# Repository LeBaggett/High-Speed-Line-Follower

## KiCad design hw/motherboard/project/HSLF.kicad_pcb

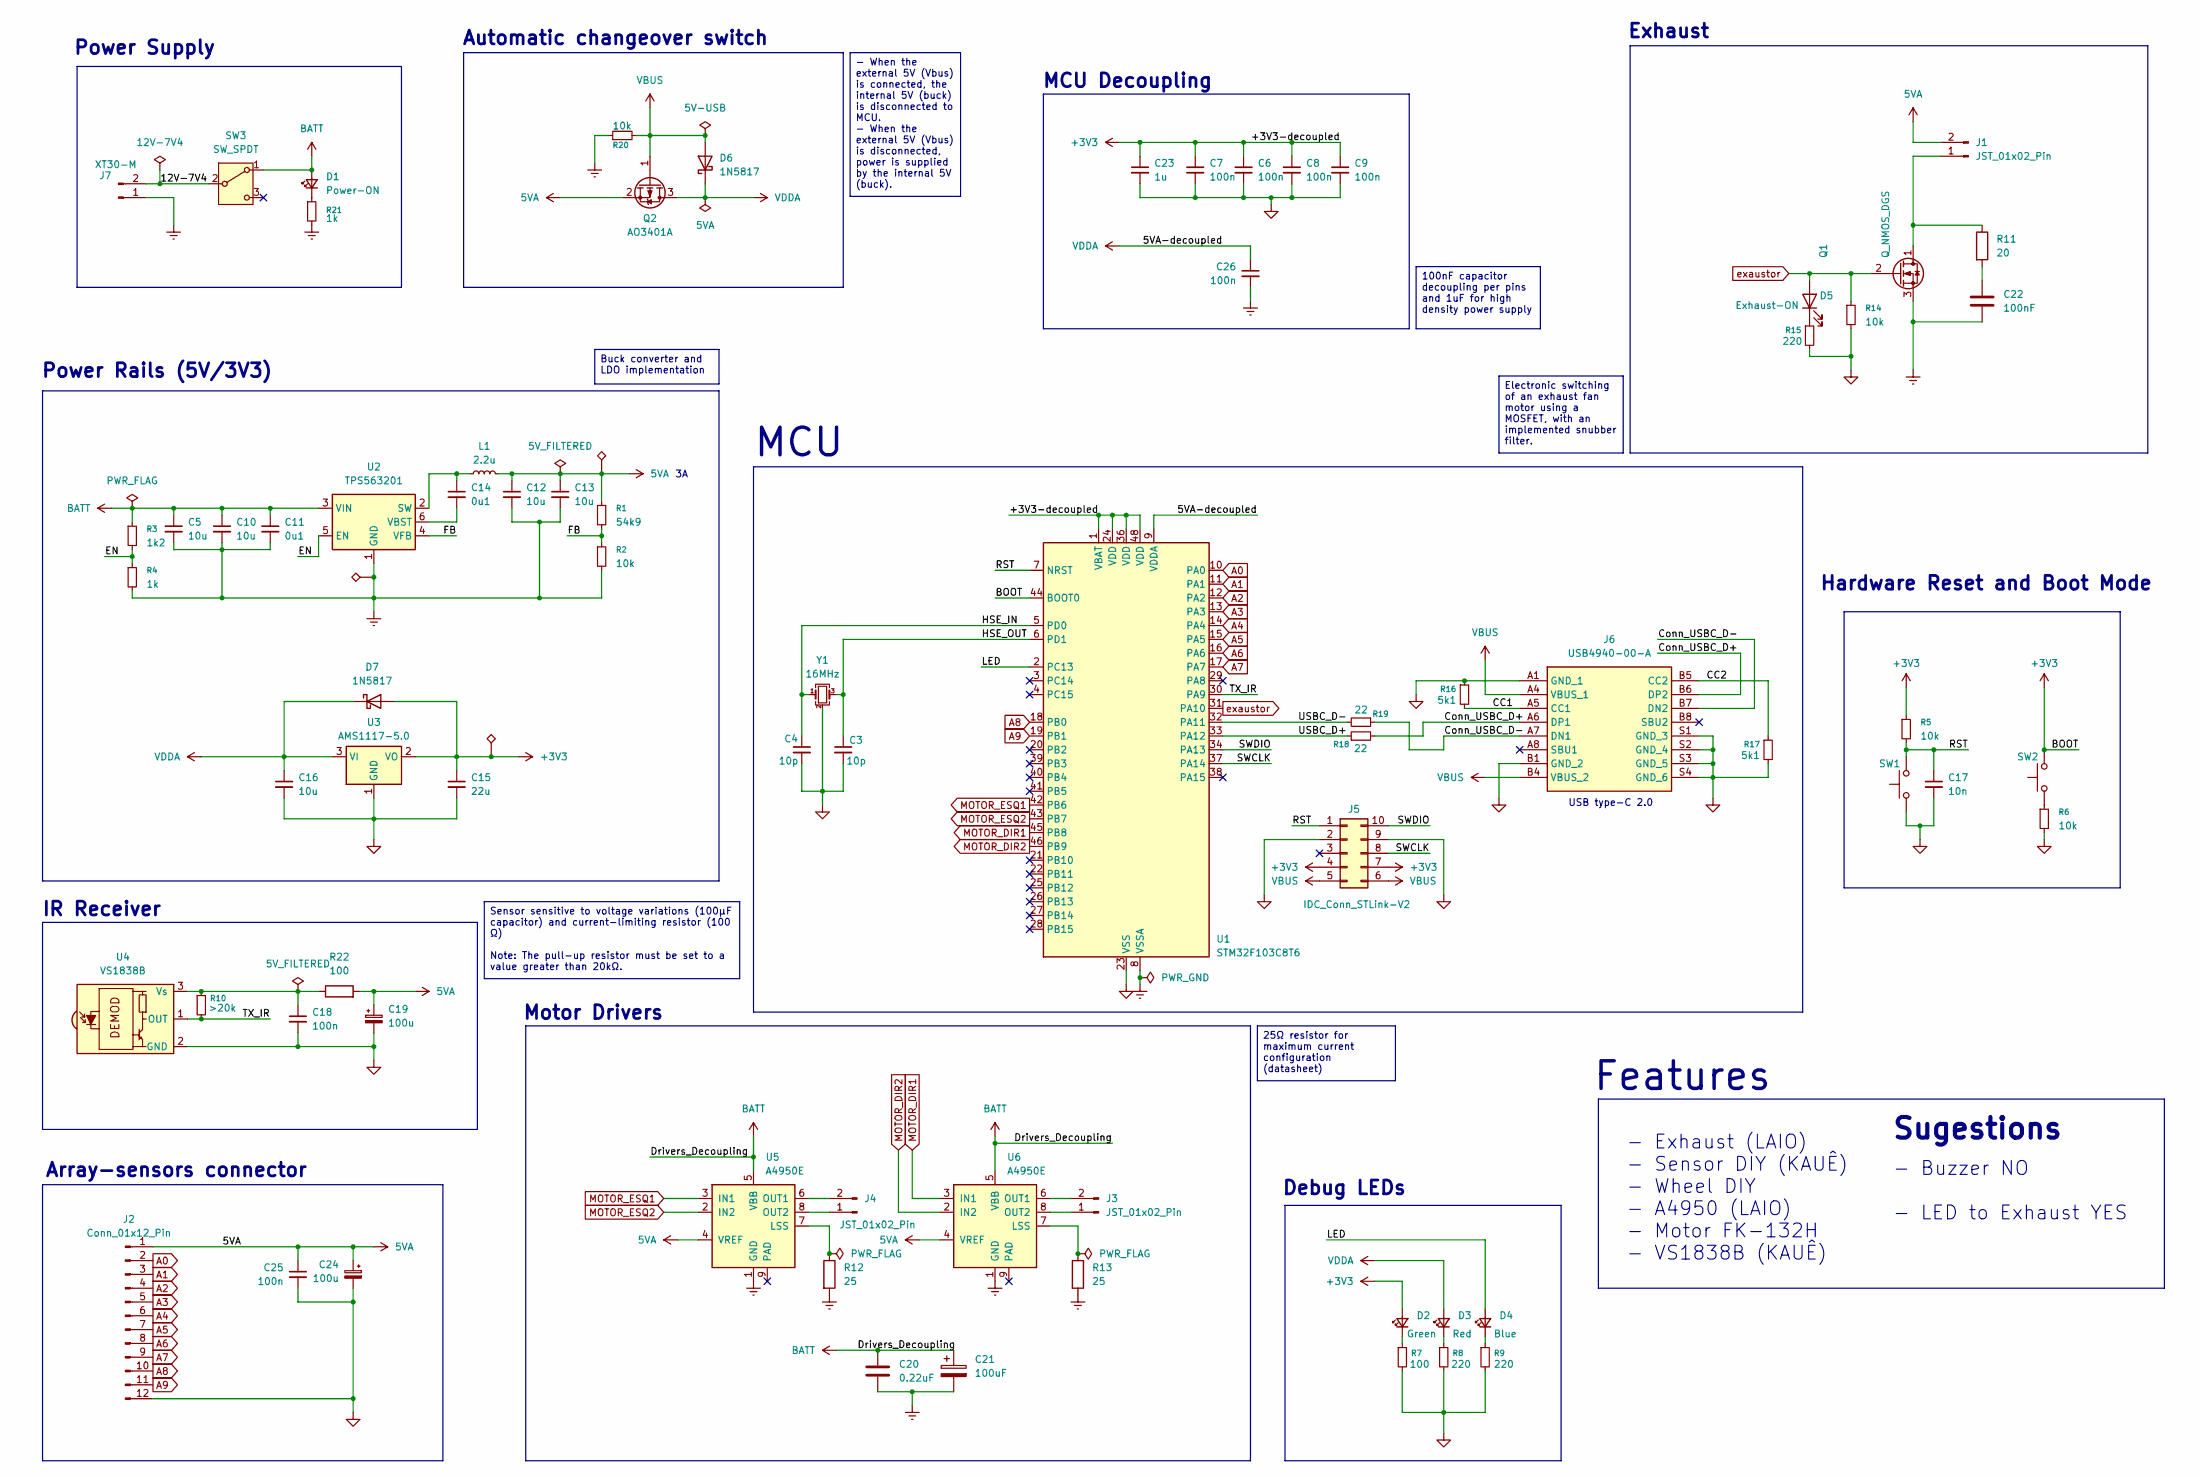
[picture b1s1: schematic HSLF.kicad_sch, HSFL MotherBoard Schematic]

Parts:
C3, C4: 10p; C_0805_2012Metric_Pad1.18x1.45mm_HandSolder
C5, C10, C12, C13, C16: 10u; C_0805_2012Metric_Pad1.18x1.45mm_HandSolder
C6, C7, C8, C9, C18, C25, C26: 100n; C_0805_2012Metric_Pad1.18x1.45mm_HandSolder
C11, C14: 0u1; C_0805_2012Metric_Pad1.18x1.45mm_HandSolder
C15: 22u; C_0805_2012Metric_Pad1.18x1.45mm_HandSolder
C17: 10n; C_0805_2012Metric_Pad1.18x1.45mm_HandSolder
C19: 100u; CP_Elec_5x3
C20: 0.22uF; C_0805_2012Metric_Pad1.18x1.45mm_HandSolder
C21: 100uF; CP_Elec_6.3x5.4
C22: 100nF; C_0805_2012Metric_Pad1.18x1.45mm_HandSolder
C23: 1u; C_0805_2012Metric_Pad1.18x1.45mm_HandSolder
C24: 100u; CP_Elec_6.3x5.4
D1: Power-ON; LED_1206_3216Metric_Pad1.42x1.75mm_HandSolder
D2: Green; LED_1206_3216Metric_Pad1.42x1.75mm_HandSolder
D3: Red; LED_1206_3216Metric_Pad1.42x1.75mm_HandSolder
D4: Blue; LED_1206_3216Metric_Pad1.42x1.75mm_HandSolder
D5: Exhaust-ON; LED_1206_3216Metric_Pad1.42x1.75mm_HandSolder
D6, D7: 1N5817; D_1206_3216Metric_Pad1.42x1.75mm_HandSolder
J1, J3, J4: JST_01x02_Pin; JST_XH_B2B-XH-A_1x02_P2.50mm_Vertical
J2: Conn_01x12_Pin; JST_XH_B12B-XH-A_1x12_P2.50mm_Vertical
J5: IDC_Conn_STLink-V2; IDC-Header_2x05_P2.54mm_Vertical
J6: USB4940-00-A; USB494000A; Manufacturer_Part_Number USB4940-00-A
J7: XT30-M; AMASS_XT30UPB-M_1x02_P5.0mm_Vertical
L1: 2.2u; L_APV_APH0618
Q1: Q_NMOS_DGS; TSOT-23_HandSoldering
Q2: AO3401A; SOT-23
R1: 54k9; R_0805_2012Metric_Pad1.20x1.40mm_HandSolder
R2, R5, R6, R14, R20: 10k; R_0805_2012Metric_Pad1.20x1.40mm_HandSolder
R3: 1k2; R_0805_2012Metric_Pad1.20x1.40mm_HandSolder
R4, R21: 1k; R_0805_2012Metric_Pad1.20x1.40mm_HandSolder
R7, R22: 100; R_0805_2012Metric_Pad1.20x1.40mm_HandSolder
R8, R9, R15: 220; R_0805_2012Metric_Pad1.20x1.40mm_HandSolder
R10: >20k; R_0805_2012Metric_Pad1.20x1.40mm_HandSolder
R11: 20; R_0805_2012Metric_Pad1.20x1.40mm_HandSolder
R12, R13: 25; R_0805_2012Metric_Pad1.20x1.40mm_HandSolder
R16, R17: 5k1; R_0805_2012Metric_Pad1.20x1.40mm_HandSolder
R18, R19: 22; R_0805_2012Metric_Pad1.20x1.40mm_HandSolder
SW1, SW2: SW_Push; SW_Push_1P1T_NO_E-Switch_TL3301NxxxxxG
SW3: SW_SPDT; SW_Slide_SPDT_Straight_CK_OS102011MS2Q
TP1, TP2, TP3: TestPoint_Alt; TestPoint_Pad_1.0x1.0mm
U1: STM32F103C8T6; LQFP-48_7x7mm_P0.5mm
U2: TPS563201; SOT-23-6_Handsoldering
U3: AMS1117-5.0; SOT-223-3_TabPin2
U4: VS1838B; Vishay_MOLD-3Pin
U5, U6: A4950E; SOIC-8-1EP_3.9x4.9mm_P1.27mm_EP2.41x3.3mm
Y1: 16MHz; Crystal_SMD_3225-4Pin_3.2x2.5mm_HandSoldering

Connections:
5VA: C12.1, C13.1, C19.1, C24.1, C25.1, J1.2, J2.1, L1.2, Q2.2 (S), R1.1, R22.2, TP2.1 (1_1), U5.4 (VREF), U6.4 (VREF)
+3V3: C6.1, C7.1, C8.1, C9.1, C15.1, C23.1, D2.2 (A), D7.2 (A), J5.4, J5.7, R5.1, SW2.2, TP3.1 (1_1), U1.1 (VBAT), U1.24 (VDD), U1.36 (VDD), U1.44 (BOOT0), U1.48 (VDD), U3.2 (VO)
/12V-7V4: J7.2, SW3.2 (B)
/CC1: J6.A5 (CC1), R16.2
/CC2: J6.B5 (CC2), R17.1
/Conn_USBC_D+: J6.A6 (DP1), J6.B6 (DP2), R18.2
/Conn_USBC_D-: J6.A7 (DN1), J6.B7 (DN2), R19.1
/EN: R3.2, R4.1, U2.5 (EN)
/FB: R1.2, R2.1, U2.4 (VFB)
/HSE_IN: C4.1, U1.5 (PD0), Y1.1
/HSE_OUT: C3.1, U1.6 (PD1), Y1.3
/LED: D4.2 (A), U1.2 (PC13)
/RST: C17.1, J5.1, R5.2, SW1.2, U1.7 (NRST)
/SWCLK: J5.8, U1.37 (PA14)
/SWDIO: J5.10, U1.34 (PA13)
/TX_IR: R10.2, U1.30 (PA9), U4.1 (OUT)
/USBC_D+: R18.1, U1.33 (PA12)
/USBC_D-: R19.2, U1.32 (PA11)
A0: J2.2, U1.10 (PA0)
A1: J2.3, U1.11 (PA1)
A2: J2.4, U1.12 (PA2)
A3: J2.5, U1.13 (PA3)
A4: J2.6, U1.14 (PA4)
A5: J2.7, U1.15 (PA5)
A6: J2.8, U1.16 (PA6)
A7: J2.9, U1.17 (PA7)
A8: J2.10, U1.18 (PB0)
A9: J2.11, U1.19 (PB1)
BATT: C5.1, C10.1, C11.1, C20.1, C21.1, D1.2 (A), R3.1, SW3.1 (A), U2.3 (VIN), U5.5 (VBB), U6.5 (VBB)
GND: C3.2, C4.2, C5.2, C6.2, C7.2, C8.2, C9.2, C10.2, C11.2, C12.2, C13.2, C15.2, C16.2, C17.2, C18.2, C19.2, C20.2, C21.2, C22.2, C23.2, C24.2, C25.2, C26.2, J2.12, J5.2, J5.9, J6.A1 (GND_1), J6.B1 (GND_2), J6.S1 (GND_3), J6.S2 (GND_4), J6.S3 (GND_5), J6.S4 (GND_6), J7.1, Q1.3 (S), R2.2, R4.2, R6.2, R7.2, R8.2, R9.2, R12.2, R13.2, R14.2, R15.2, R16.1, R17.2, R20.1, R21.2, SW1.1, TP1.1 (1_1), U1.8 (VSSA), U1.23 (VSS), U1.35 (VSS), U1.47 (VSS), U2.1 (GND), U3.1 (GND), U4.2 (GND), U5.1 (GND), U6.1 (GND), Y1.2 (G), Y1.4 (G)
MOTOR_DIR1: U1.45 (PB8), U6.3 (IN1)
MOTOR_DIR2: U1.46 (PB9), U6.2 (IN2)
MOTOR_ESQ1: U1.42 (PB6), U5.3 (IN1)
MOTOR_ESQ2: U1.43 (PB7), U5.2 (IN2)
unnamed: C22.1, R11.2
unnamed: D1.1 (K), R21.1
unnamed: D2.1 (K), R7.1
unnamed: D3.1 (K), R8.1
unnamed: D4.1 (K), R9.1
unnamed: D5.1 (K), R15.1
unnamed: J1.1, Q1.1 (D), R11.1
unnamed: J3.1, U6.8 (OUT2)
unnamed: J3.2, U6.6 (OUT1)
unnamed: J4.1, U5.8 (OUT2)
unnamed: J4.2, U5.6 (OUT1)
unnamed: R6.1, SW2.1
unnamed: C14.1, L1.1, U2.2 (SW)
unnamed: C14.2, U2.6 (VBST)
unnamed: C18.1, R10.1, R22.1, U4.3 (Vs)
unnamed: R12.1, U5.7 (LSS)
unnamed: R13.1, U6.7 (LSS)
VBUS: D6.2 (A), J5.5, J5.6, J6.A4 (VBUS_1), J6.B4 (VBUS_2), Q2.1 (G), R20.2
VDDA: C16.1, C26.1, D3.2 (A), D6.1 (K), D7.1 (K), Q2.3 (D), U1.9 (VDDA), U3.3 (VI)
exaustor: D5.2 (A), Q1.2 (G), R14.1, U1.31 (PA10)

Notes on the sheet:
Array-sensors connector
Hardware Reset and Boot Mode
MCU Decoupling
Features
USB type-C 2.0
Power Supply
Exhaust
- Exhaust (LAIO) - Sensor DIY (KAUÊ) - Wheel DIY - A4950 (LAIO) - Motor FK-132H - VS1838B (KAUÊ)
Motor Drivers
Power Rails (5V/3V3)
Debug LEDs
Automatic changeover switch
- Buzzer NO - LED to Exhaust YES
MCU
Sugestions
IR Receiver
- When the external 5V (Vbus) is connected, the internal 5V (buck) is disconnected to MCU. - When the external 5V (Vbus) is disconnected, power is supplied by the internal 5V (buck).
Electronic switching of an exhaust fan motor using a MOSFET, with an implemented snubber filter.
Sensor sensitive to voltage variations (100µF capacitor) and current-limiting resistor (100 Ω) Note: The pull-up resistor must be set to a value greater than 20kΩ.
100nF capacitor decoupling per pins and 1uF for high density power supply
Buck converter and LDO implementation
25Ω resistor for maximum current configuration (datasheet)

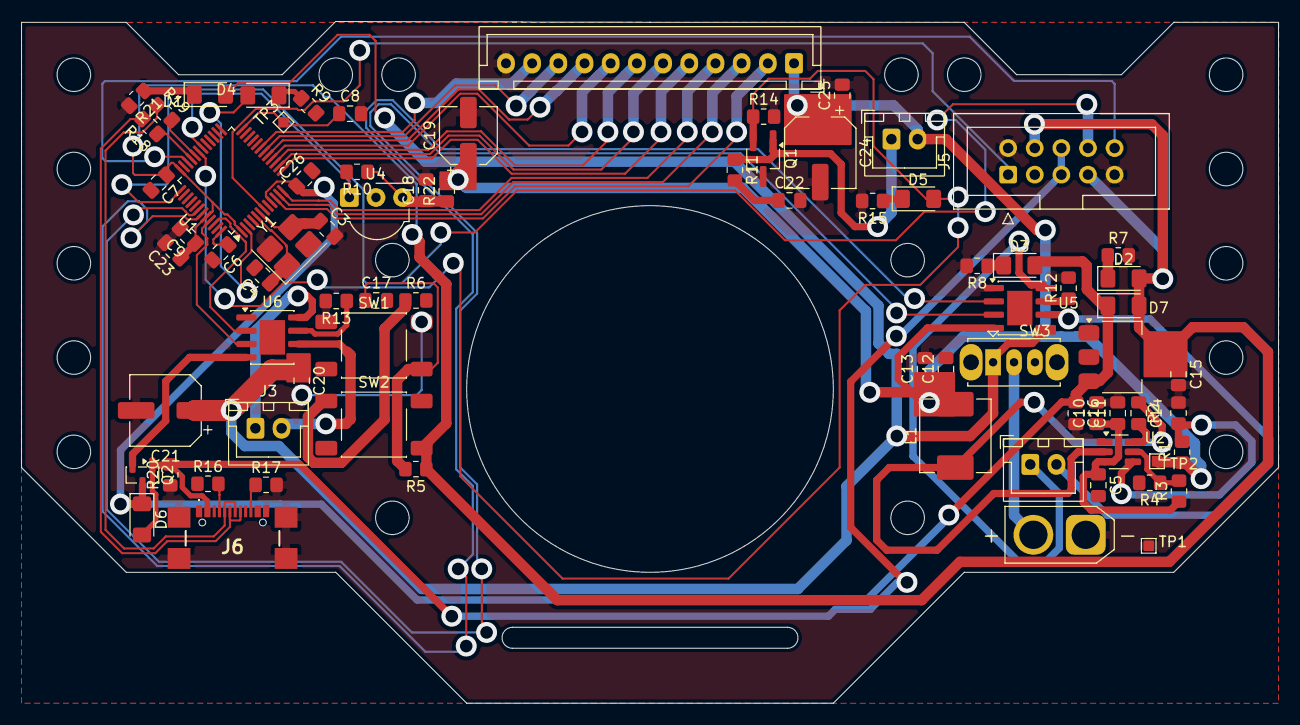
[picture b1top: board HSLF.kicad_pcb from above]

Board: 2 copper layers, 120.0 x 65.1 mm, 76 parts (0 on the bottom side), 54 nets.

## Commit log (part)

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2026-05-11 Revise license details and add CERN-OHL-P
    Updated copyright holder name and added CERN Open Hardware License.
2026-05-12 Add a Altimu PCB project and the premisse Power Management schematic
2026-05-12 Add README.md with project title
2026-05-12 add READMEs for show the files
2026-05-14 Complete motherboard schematic v3
2026-05-14 complete schematic motherboard
2026-05-14 revision and modification schematic, adding GND Plane, Bypass capacitors and Better design
2026-05-17 motherboard Schematic and PCB fineshed !
2026-06-10 miau
